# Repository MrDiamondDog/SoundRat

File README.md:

# SoundRat

A desktop sound mixer for controlling the volumes of applications on your computer. This repo contains CAD, PCB, firmware, and software.

Includes 5 rotary encoders (with buttons!), 16 RGB LEDs, and an RP2040-zero microcontroller, all on a custom PCB in a custom case!

The software runs on your computer and reads from SoundRat to update application volumes, the firmware simply sends that data over and receives volume/peak data.

I made this project as a replacement for my very crude Deej that performs a similar function. It is simply an Arduino Uno and 5 linear potentiometers and does its job, but leaves much to be desired. I wanted more out of it, especially being a sound guy at my school's theatre, I wanted to see the volume levels accurately (cause the linear pots are really terrible), and peak level LED indicators (basically visualizing the current volume of the audio outputting from the application). Deej is a really cool project, as it is just an Arduino project you load onto a nano and software that runs really nicely. It's easily customizable and I hope to do that here as well. I've already found a lot of use out of my Deej, and I figured it would make a good project to make a spirtual successor.

A lot of inspiration is taken from Deej (check it out [here](https://github.com/omriharel/deej)), but all designs are by me!

## Images

Case

Routing

PCB

Schematic

Full Assembly

## BOM

All items from Aliexpress

| Name | Qtd | Price | Shipping | Link |
| ---- | --- | ----- | -------- | ---- |
| RP2040-Zero RP2040 for Raspberry Pi Microcontroller PICO Development Board Module Dual-core Cortex M0+ Processor 2MB Flash | 1 | $1.99 | $0 | https://www.aliexpress.us/item/3256807207087581.html?mp=1&pdp_npi=6%40dis!USD!USD%208.03!USD%201.99!!USD%201.99!!!%402103126e17712032175756586e399f!12000040563329988!ct!US!6602055344!!1!0!&gatewayAdapt=glo2usa |
| 5PCS 360 Degree Rotary Encoder EC12 RE12 Audio Encoder Coding 5Pin 24 Position With Push Button Switch Handle Length 12.5MM | 1x5pcs | $2.56 | $0 | https://www.aliexpress.us/item/3256801922952476.html?mp=1&pdp_npi=6%40dis!USD!USD%202.44!USD%202.36!!USD%202.36!!!%402103126e17712032175756586e399f!12000018768589822!ct!US!6602055344!!1!0!&gatewayAdapt=glo2usa |
| 2~1000Pcs 4 Color in 1 SK6812 RGBW RGBWW RGBNW WWA RGB White SMD 3535 5050 Individually Addressable LED Chip Pixel as WS2812B 5V | 2x10pcs | $5.03 | $3.98 | https://www.aliexpress.us/item/2251832480376635.html?mp=1&pdp_npi=6%40dis!USD!USD%205.18!USD%205.03!!USD%205.03!!!%402103126e17712032175756586e399f!12000038354525581!ct!US!6602055344!!2!0!&gatewayAdapt=glo2usa |
| PCB from JLCPCB | 1x5pcs | $2.00 | $3.12 |

**Total**: $23.77

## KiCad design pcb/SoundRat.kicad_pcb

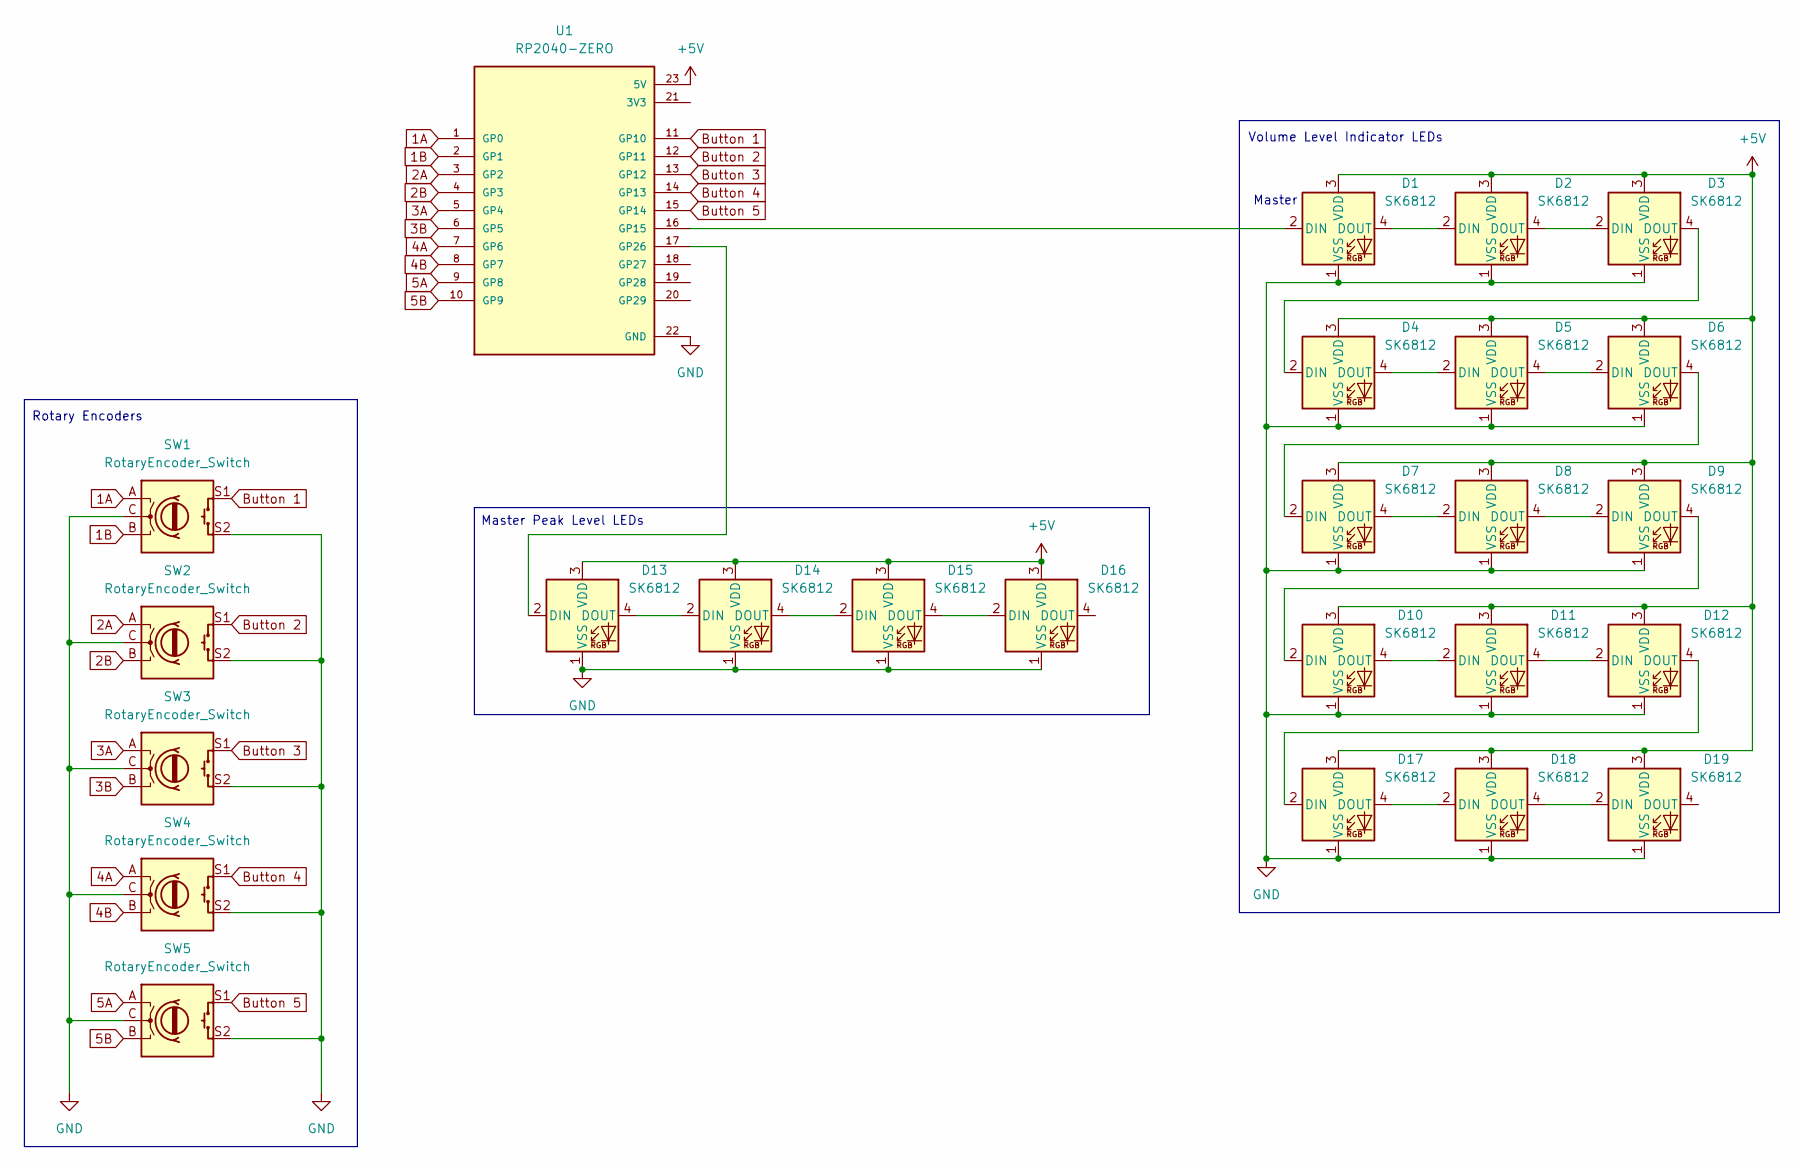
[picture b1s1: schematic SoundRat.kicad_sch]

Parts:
D1, D2, D3, D4, D5, D6, D7, D8, D9, D10, D11, D12, D13, D14, D15, D16, D17, D18, D19: SK6812; LED_SK6812_PLCC4_5.0x5.0mm_P3.2mm
SW1, SW2, SW3, SW4, SW5: RotaryEncoder_Switch; RotaryEncoder_Bourns_Vertical_PEC12R-3x17F-Sxxxx
U1: RP2040-ZERO; MODULE_RP2040-ZERO; PARTREV NA

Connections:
1A: SW1.A, U1.1 (GP0)
1B: SW1.B, U1.2 (GP1)
2A: SW2.A, U1.3 (GP2)
2B: SW2.B, U1.4 (GP3)
3A: SW3.A, U1.5 (GP4)
3B: SW3.B, U1.6 (GP5)
4A: SW4.A, U1.7 (GP6)
4B: SW4.B, U1.8 (GP7)
5A: SW5.A, U1.9 (GP8)
5B: SW5.B, U1.10 (GP9)
+5V: D1.3 (VDD), D2.3 (VDD), D3.3 (VDD), D4.3 (VDD), D5.3 (VDD), D6.3 (VDD), D7.3 (VDD), D8.3 (VDD), D9.3 (VDD), D10.3 (VDD), D11.3 (VDD), D12.3 (VDD), D13.3 (VDD), D14.3 (VDD), D15.3 (VDD), D16.3 (VDD), D17.3 (VDD), D18.3 (VDD), D19.3 (VDD), U1.23 (5V)
Button 1: SW1.S1, U1.11 (GP10)
Button 2: SW2.S1, U1.12 (GP11)
Button 3: SW3.S1, U1.13 (GP12)
Button 4: SW4.S1, U1.14 (GP13)
Button 5: SW5.S1, U1.15 (GP14)
GND: D1.1 (VSS), D2.1 (VSS), D3.1 (VSS), D4.1 (VSS), D5.1 (VSS), D6.1 (VSS), D7.1 (VSS), D8.1 (VSS), D9.1 (VSS), D10.1 (VSS), D11.1 (VSS), D12.1 (VSS), D13.1 (VSS), D14.1 (VSS), D15.1 (VSS), D16.1 (VSS), D17.1 (VSS), D18.1 (VSS), D19.1 (VSS), SW1.C, SW1.S2, SW2.C, SW2.S2, SW3.C, SW3.S2, SW4.C, SW4.S2, SW5.C, SW5.S2, U1.22 (GND)
unnamed: D1.2 (DIN), U1.16 (GP15)
unnamed: D1.4 (DOUT), D2.2 (DIN)
unnamed: D2.4 (DOUT), D3.2 (DIN)
unnamed: D3.4 (DOUT), D4.2 (DIN)
unnamed: D4.4 (DOUT), D5.2 (DIN)
unnamed: D5.4 (DOUT), D6.2 (DIN)
unnamed: D6.4 (DOUT), D7.2 (DIN)
unnamed: D7.4 (DOUT), D8.2 (DIN)
unnamed: D8.4 (DOUT), D9.2 (DIN)
unnamed: D9.4 (DOUT), D10.2 (DIN)
unnamed: D10.4 (DOUT), D11.2 (DIN)
unnamed: D11.4 (DOUT), D12.2 (DIN)
unnamed: D12.4 (DOUT), D17.2 (DIN)
unnamed: D13.2 (DIN), U1.17 (GP26)
unnamed: D13.4 (DOUT), D14.2 (DIN)
unnamed: D14.4 (DOUT), D15.2 (DIN)
unnamed: D15.4 (DOUT), D16.2 (DIN)
unnamed: D17.4 (DOUT), D18.2 (DIN)
unnamed: D18.4 (DOUT), D19.2 (DIN)

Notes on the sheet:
Master Peak Level LEDs
Rotary Encoders
Volume Level Indicator LEDs
Master

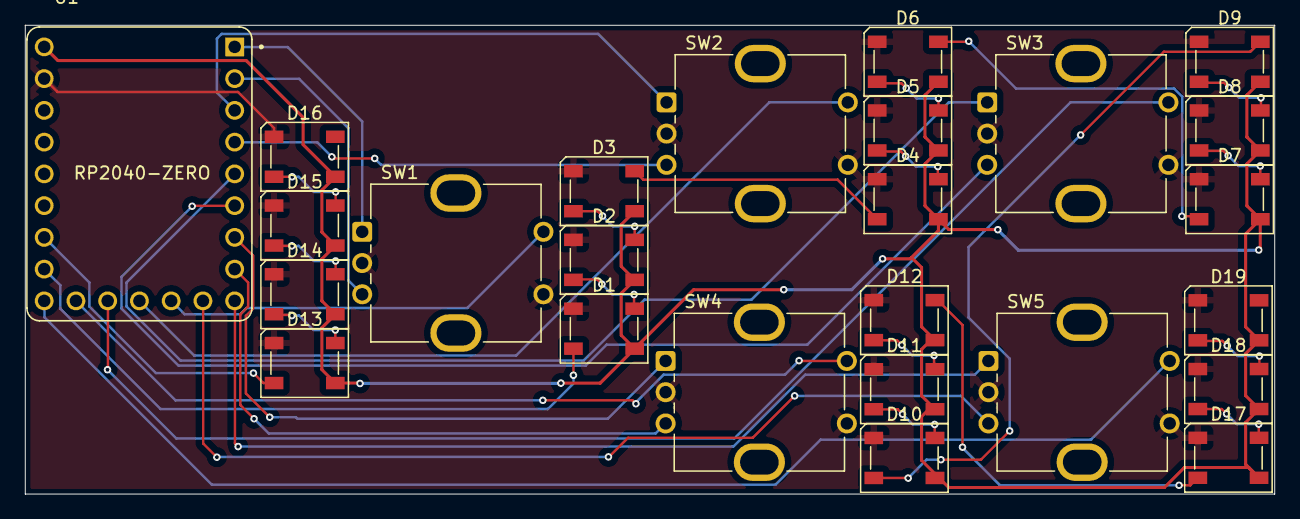
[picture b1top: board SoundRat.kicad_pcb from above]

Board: 2 copper layers, 99.9 x 37.5 mm, 25 parts (0 on the bottom side), 36 nets.

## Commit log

2026-02-16 Init
2026-02-16 Add README.md
2026-02-16 Add gerbers and BOM
